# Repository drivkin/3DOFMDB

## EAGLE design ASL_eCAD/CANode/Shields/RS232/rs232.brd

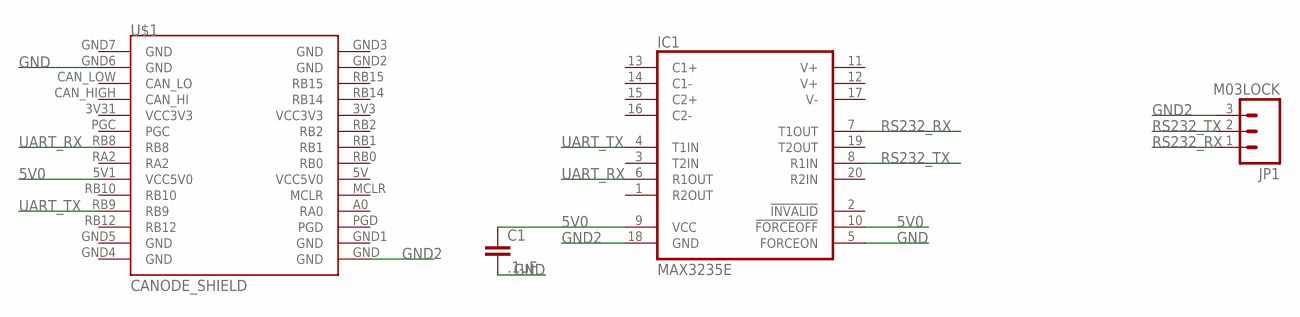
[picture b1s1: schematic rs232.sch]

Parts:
C1: .1uF; 1206
IC1: MAX3235E; SO20L
JP1: M03LOCK; 1X03_LOCK
U$1: CANODE_SHIELD

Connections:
5V0: C1.1, IC1.9 (VCC), IC1.10 (!FORCEOFF), U$1.5V1 (VCC5V0)
GND: C1.2, IC1.5 (FORCEON), U$1.GND6 (GND)
GND2: IC1.18 (GND), JP1.3, U$1.GND
RS232_RX: IC1.7 (T1OUT), JP1.1
RS232_TX: IC1.8 (R1IN), JP1.2
UART_RX: IC1.6 (R1OUT), U$1.RB8
UART_TX: IC1.4 (T1IN), U$1.RB9

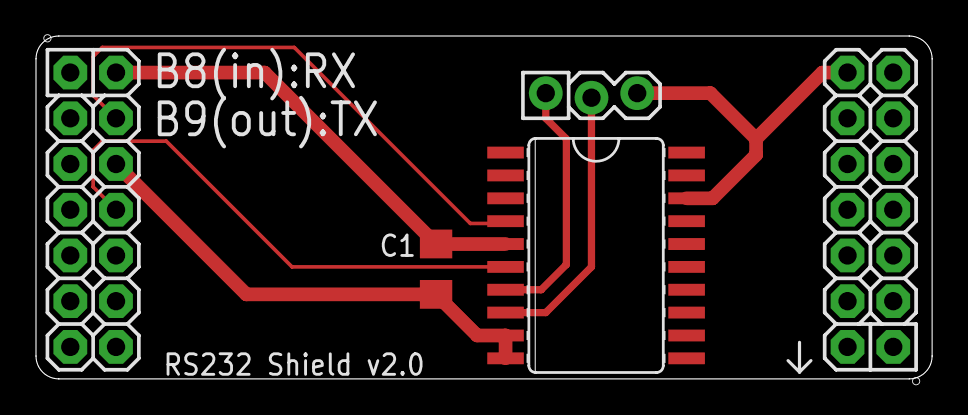
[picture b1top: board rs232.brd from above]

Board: 2 copper layers, 49.8 x 19.0 mm, 4 parts (0 on the bottom side), 7 nets.

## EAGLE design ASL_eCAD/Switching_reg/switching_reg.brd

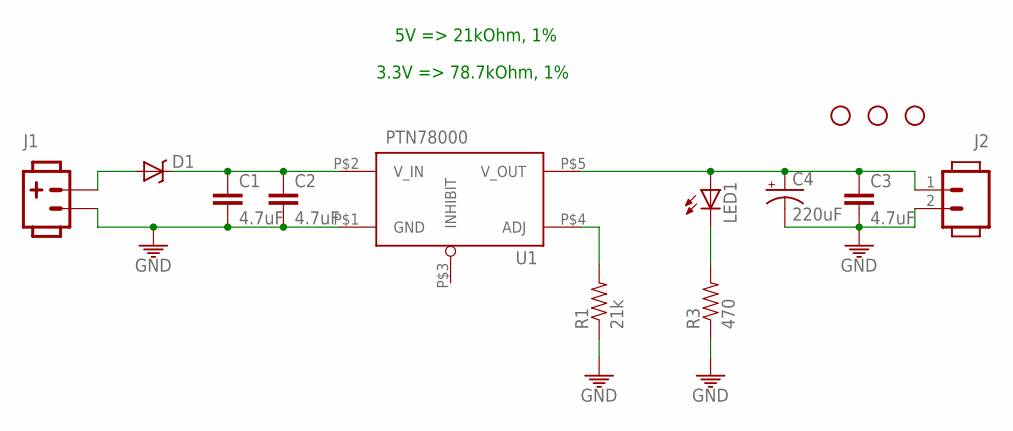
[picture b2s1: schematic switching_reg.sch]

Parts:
C1, C2, C3: 4.7uF; 1206
C4: 220uF; CPOL_6.6
D1: DIODE-SCHOTTKY240A; SMA-DIODE-B240A
J1: POW_CONNECTMALE; SOCKET-MALE-3.96MM-2
J2: SCREWTERM02; SCREW_TERMINAL-5.08MM-2
JP1, JP2, JP3: STAND-OFFTIGHT; STAND-OFF-TIGHT
LED1: LED1206; LED-1206
R1: 21k; 0805
R3: 470; 0805
U1: PTN78000; PTN78000_SM

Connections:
GND: C1.2, C2.2, C3.2, C4.-, J1.P$2 (2), J2.2, R1.1, R3.1, U1.P$1 (GND)
unnamed: D1.A, J1.P$1 (1)
unnamed: C1.1, C2.1, D1.C, U1.P$2 (V_IN)
unnamed: C3.1, C4.+, J2.1, LED1.A, U1.P$5 (V_OUT)
unnamed: R1.2, U1.P$4 (ADJ)
unnamed: LED1.C, R3.2

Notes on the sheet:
3.3V => 78.7kOhm, 1%
5V => 21kOhm, 1%

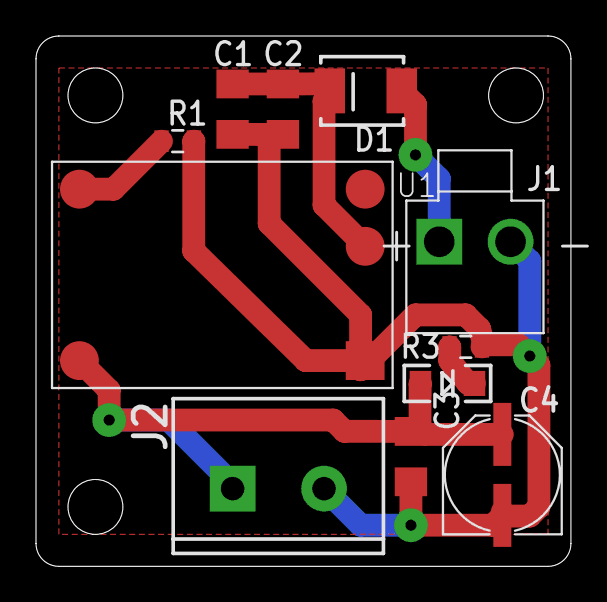
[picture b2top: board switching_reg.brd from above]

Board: 2 copper layers, 29.7 x 29.5 mm, 14 parts (0 on the bottom side), 6 nets.
